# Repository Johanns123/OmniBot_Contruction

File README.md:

# OmniBot_Contruction
 This repository has all the documents of the robot's assembly

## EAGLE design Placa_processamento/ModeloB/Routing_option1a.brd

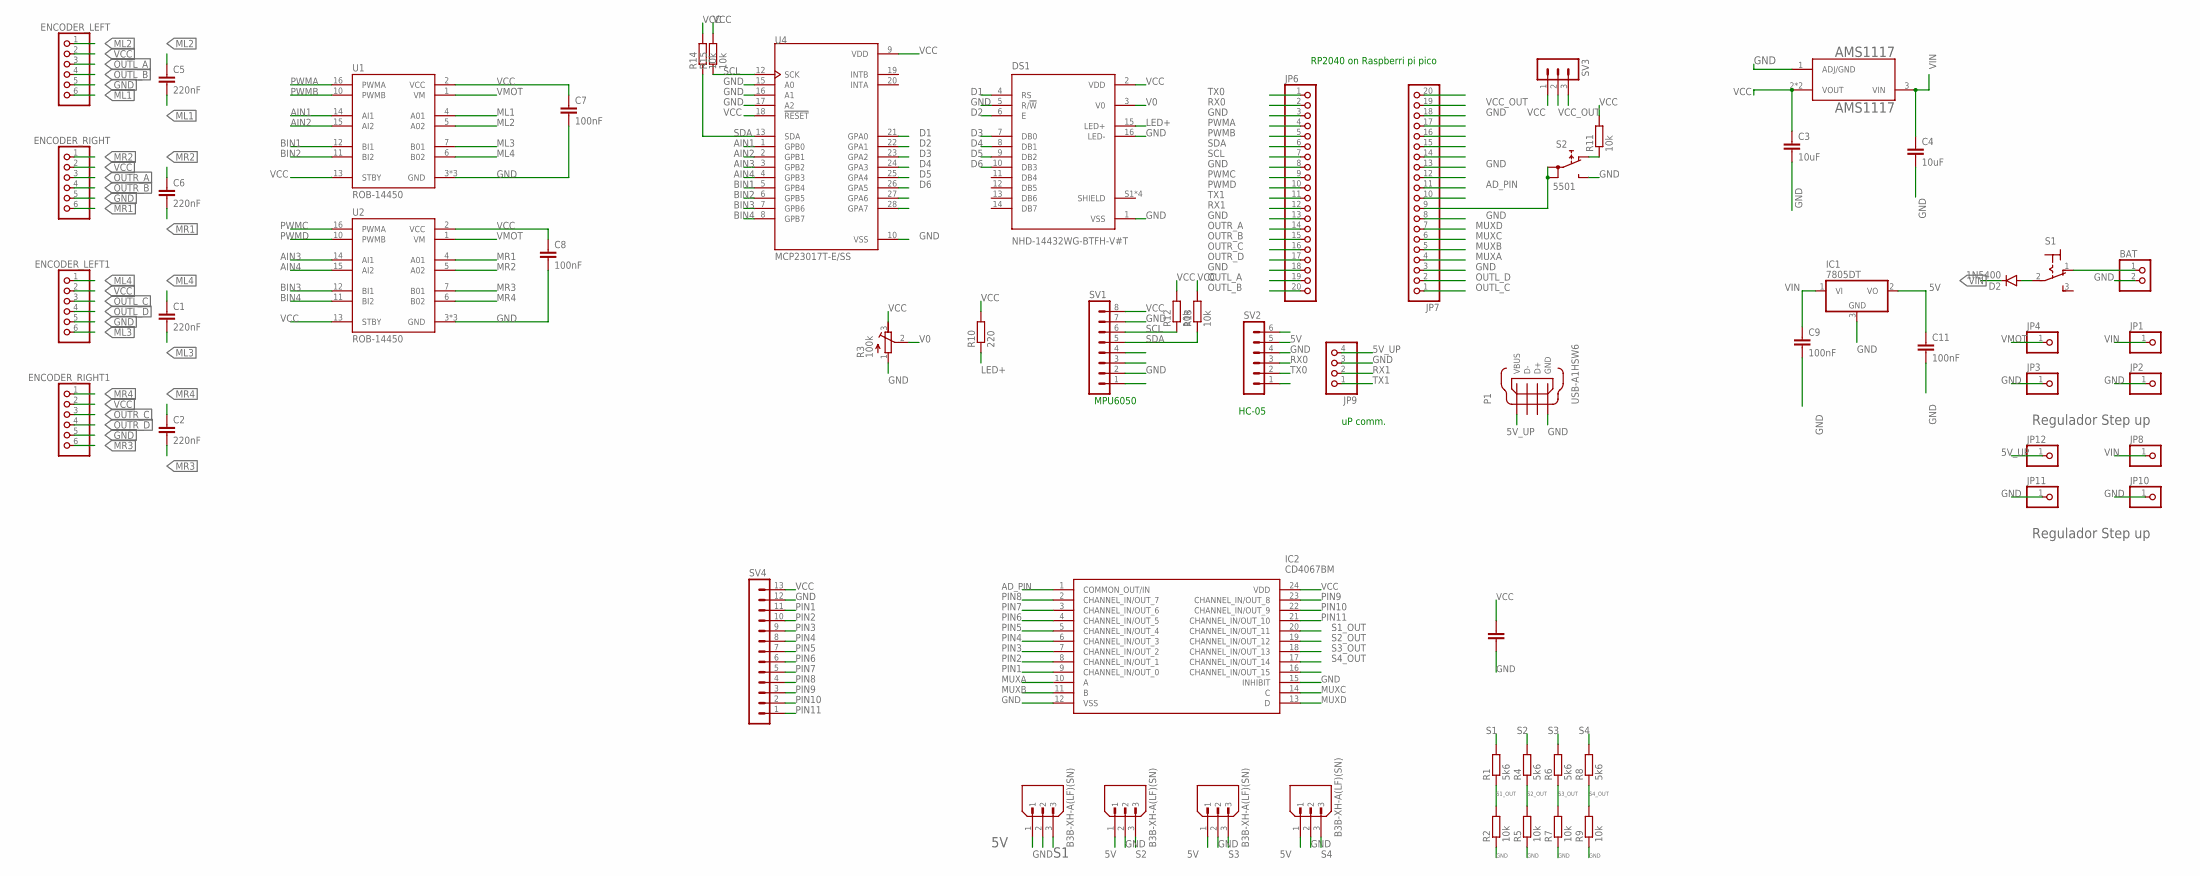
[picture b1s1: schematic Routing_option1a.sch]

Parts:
AMS1117: AMS1117; SOT229P700X180-4N
BAT: PINHD-1X2; 1X02
C1, C2, C5, C6: 220nF; C0805
C3, C4: 10uF; C0805
C7, C8, C9, C10, C11: 100nF; C0805
D2: 1N5400; DO201-15
DIR: B3B-XH-A(LF)(SN); JST_B3B-XH-A(LF)(SN)
DS1: NHD-14432WG-BTFH-V#T; LCD_NHD-14432WG-BTFH-V#T
ENCODER_LEFT, ENCODER_LEFT1: PINHD-1X6; 1X06
ENCODER_RIGHT, ENCODER_RIGHT1: PINHD-1X6; 1X06
ESQ: B3B-XH-A(LF)(SN); JST_B3B-XH-A(LF)(SN)
FRENT: B3B-XH-A(LF)(SN); JST_B3B-XH-A(LF)(SN)
IC1: 7805DT; TO252
IC2: CD4067BM; SOIC127P1030X265-24N
JP1, JP2, JP3, JP4, JP8, JP10, JP11, JP12: PINHD-1X1; 1X01
JP6, JP7: PINHD-1X20; 1X20
JP9: PINHD-1X4; 1X04
P1: USB-A1HSW6; OST_USB-A1HSW6
R1, R4, R6, R8: 5k6; R0805
R2, R5, R7, R9, R11, R12, R13, R14, R15: 10k; R0805
R3: 100k; RTRIM64W
R10: 220; R0805
S1: 320-916
S2: 5501
SV1: MA08-1
SV2: MA06-1
SV3: MA03-1
SV4: MA13-1
TRAS: B3B-XH-A(LF)(SN); JST_B3B-XH-A(LF)(SN)
U1, U2: ROB-14450; MODULE_ROB-14450
U4: MCP23017T-E/SS; SOP65P780X200-28N

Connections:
5V: C11.1, DIR.1, ESQ.1, FRENT.1, IC1.2 (VO), SV2.5, TRAS.1
5V_UP: JP9.4, JP12.1, P1.1 (VBUS)
AD1: JP7.12
AD2: JP7.14
AD_PIN: IC2.1 (COMMON_OUT/IN), JP7.11
AIN1: U1.14 (AI1), U4.1 (GPB0)
AIN2: U1.15 (AI2), U4.2 (GPB1)
AIN3: U2.14 (AI1), U4.3 (GPB2)
AIN4: U2.15 (AI2), U4.4 (GPB3)
BIN1: U1.12 (BI1), U4.5 (GPB4)
BIN2: U1.11 (BI2), U4.6 (GPB5)
BIN3: U2.12 (BI1), U4.7 (GPB6)
BIN4: U2.11 (BI2), U4.8 (GPB7)
D1: DS1.4 (RS), U4.21 (GPA0)
D2: DS1.6 (E), U4.22 (GPA1)
D3: DS1.7 (DB0), U4.23 (GPA2)
D4: DS1.8 (DB1), U4.24 (GPA3)
D5: DS1.9 (DB2), U4.25 (GPA4)
D6: DS1.10 (DB3), U4.26 (GPA5)
GND: AMS1117.1 (ADJ/GND), BAT.2, C3.2, C4.2, C7.2, C8.2, C9.2, C10.2, C11.2, DIR.2, DS1.1 (VSS), DS1.5 (R/!W), DS1.16 (LED-), ENCODER_LEFT.5, ENCODER_LEFT1.5, ENCODER_RIGHT.5, ENCODER_RIGHT1.5, ESQ.2, FRENT.2, IC1.3 (GND), IC2.12 (VSS), IC2.15 (INHIBIT), JP2.1, JP3.1, JP6.3, JP6.8, JP6.13, JP6.18, JP7.3, JP7.8, JP7.13, JP7.18, JP9.3, JP10.1, JP11.1, P1.4 (GND), R2.1, R3.1 (A), R5.1, R7.1, R9.1, S2.NO, SV1.2, SV1.7, SV2.4, SV4.12, TRAS.2, U1.3 (GND), U1.8 (GND), U1.9 (GND), U2.3 (GND), U2.8 (GND), U2.9 (GND), U4.10 (VSS), U4.15 (A0), U4.16 (A1), U4.17 (A2)
LED+: DS1.15 (LED+), R10.1
ML1: C5.2, ENCODER_LEFT.6, U1.4 (A01)
ML2: C5.1, ENCODER_LEFT.1, U1.5 (A02)
ML3: C1.2, ENCODER_LEFT1.6, U1.7 (B01)
ML4: C1.1, ENCODER_LEFT1.1, U1.6 (B02)
MR1: C6.2, ENCODER_RIGHT.6, U2.4 (A01)
MR2: C6.1, ENCODER_RIGHT.1, U2.5 (A02)
MR3: C2.2, ENCODER_RIGHT1.6, U2.7 (B01)
MR4: C2.1, ENCODER_RIGHT1.1, U2.6 (B02)
MUXA: IC2.10 (A), JP7.4
MUXB: IC2.11 (B), JP7.5
MUXC: IC2.14 (C), JP7.6
MUXD: IC2.13 (D), JP7.7
unnamed: D2.A, S1.2
unnamed: BAT.1, S1.1 (O)
unnamed: R11.1, S2.NC
NET$4: JP7.20
NET$5: JP7.17
NET$6: JP7.16
NET$7: JP7.15
NET$8: JP7.10
NET$15: JP7.9, S2.1A, S2.1B
OUTL_A: ENCODER_LEFT.3, JP6.19
OUTL_B: ENCODER_LEFT.4, JP6.20
OUTL_C: ENCODER_LEFT1.3, JP7.1
OUTL_D: ENCODER_LEFT1.4, JP7.2
OUTR_A: ENCODER_RIGHT.3, JP6.14
OUTR_B: ENCODER_RIGHT.4, JP6.15
OUTR_C: ENCODER_RIGHT1.3, JP6.16
OUTR_D: ENCODER_RIGHT1.4, JP6.17
PIN1: IC2.9 (CHANNEL_IN/OUT_0), SV4.11
PIN2: IC2.8 (CHANNEL_IN/OUT_1), SV4.10
PIN3: IC2.7 (CHANNEL_IN/OUT_2), SV4.9
PIN4: IC2.6 (CHANNEL_IN/OUT_3), SV4.8
PIN5: IC2.5 (CHANNEL_IN/OUT_4), SV4.7
PIN6: IC2.4 (CHANNEL_IN/OUT_5), SV4.6
PIN7: IC2.3 (CHANNEL_IN/OUT_6), SV4.5
PIN8: IC2.2 (CHANNEL_IN/OUT_7), SV4.4
PIN9: IC2.23 (CHANNEL_IN/OUT_8), SV4.3
PIN10: IC2.22 (CHANNEL_IN/OUT_9), SV4.2
PIN11: IC2.21 (CHANNEL_IN/OUT_10), SV4.1
PWMA: JP6.4, U1.16 (PWMA)
PWMB: JP6.5, U1.10 (PWMB)
PWMC: JP6.9, U2.16 (PWMA)
PWMD: JP6.10, U2.10 (PWMB)
RX0: JP6.2, SV2.3
RX1: JP6.12, JP9.2
S1: FRENT.3, R1.2
S1_OUT: IC2.20 (CHANNEL_IN/OUT_11), R1.1, R2.2
S2: ESQ.3, R4.2
S2_OUT: IC2.19 (CHANNEL_IN/OUT_12), R4.1, R5.2
S3: DIR.3, R6.2
S3_OUT: IC2.18 (CHANNEL_IN/OUT_13), R6.1, R7.2
S4: R8.2, TRAS.3
S4_OUT: IC2.17 (CHANNEL_IN/OUT_14), R8.1, R9.2
S5: IC2.16 (CHANNEL_IN/OUT_15)
SCL: JP6.7, R12.1, R15.1, SV1.6, U4.12 (SCK)
SDA: JP6.6, R13.1, R14.1, SV1.5, U4.13 (SDA)
TX0: JP6.1, SV2.2
TX1: JP6.11, JP9.1
V0: DS1.3 (V0), R3.2 (S)
VCC: AMS1117.2 (VOUT), AMS1117.4 (VOUT), C3.1, C7.1, C8.1, C10.1, DS1.2 (VDD), ENCODER_LEFT.2, ENCODER_LEFT1.2, ENCODER_RIGHT.2, ENCODER_RIGHT1.2, IC2.24 (VDD), R3.3 (E), R10.2, R11.2, R12.2, R13.2, R14.2, R15.2, SV1.8, SV3.1, SV4.13, U1.2 (VCC), U1.13 (STBY), U2.2 (VCC), U2.13 (STBY), U4.9 (VDD), U4.18 (!RESET)
VCC_OUT: JP7.19, SV3.2
VIN: AMS1117.3 (VIN), C4.1, C9.1, D2.C, IC1.1 (VI), JP1.1, JP8.1
VMOT: JP4.1, U1.1 (VM), U2.1 (VM)

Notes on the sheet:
Regulador Step up
MPU6050
HC-05
uP comm.
RP2040 on Raspberri pi pico

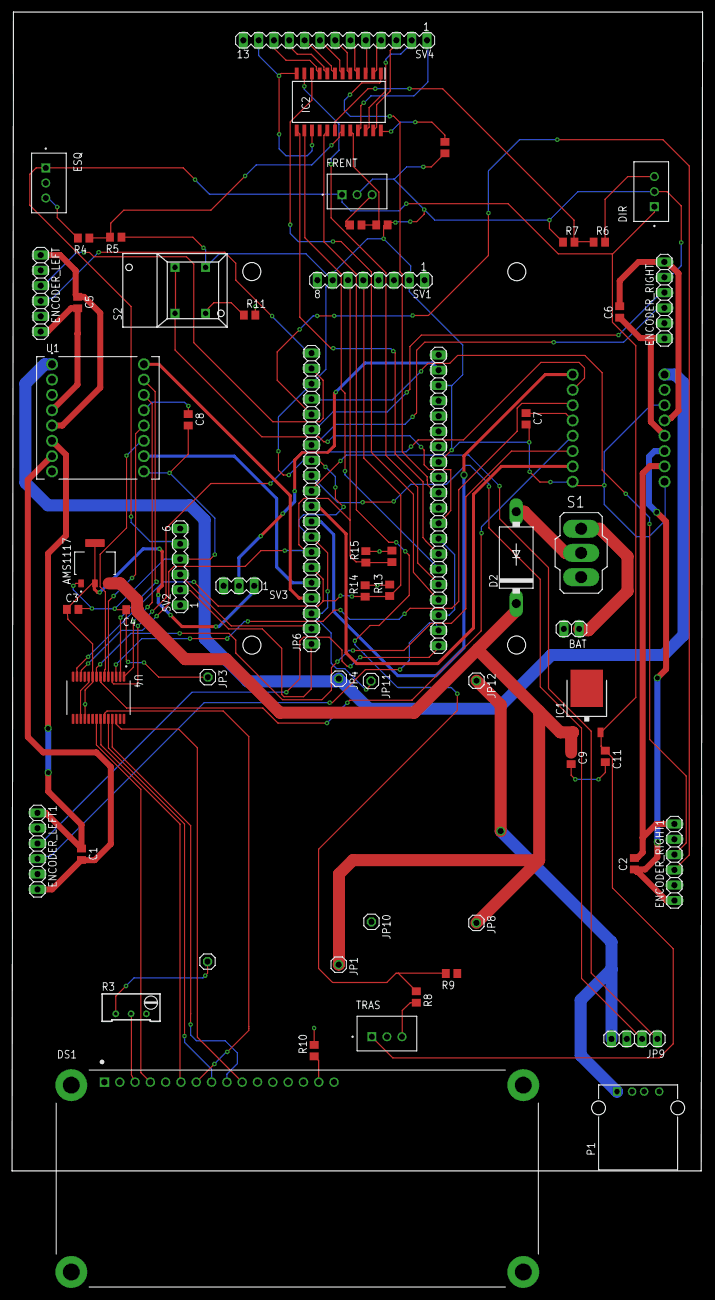
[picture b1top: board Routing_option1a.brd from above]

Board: 2 copper layers, 114.6 x 192.3 mm, 61 parts (1 on the bottom side), 77 nets.

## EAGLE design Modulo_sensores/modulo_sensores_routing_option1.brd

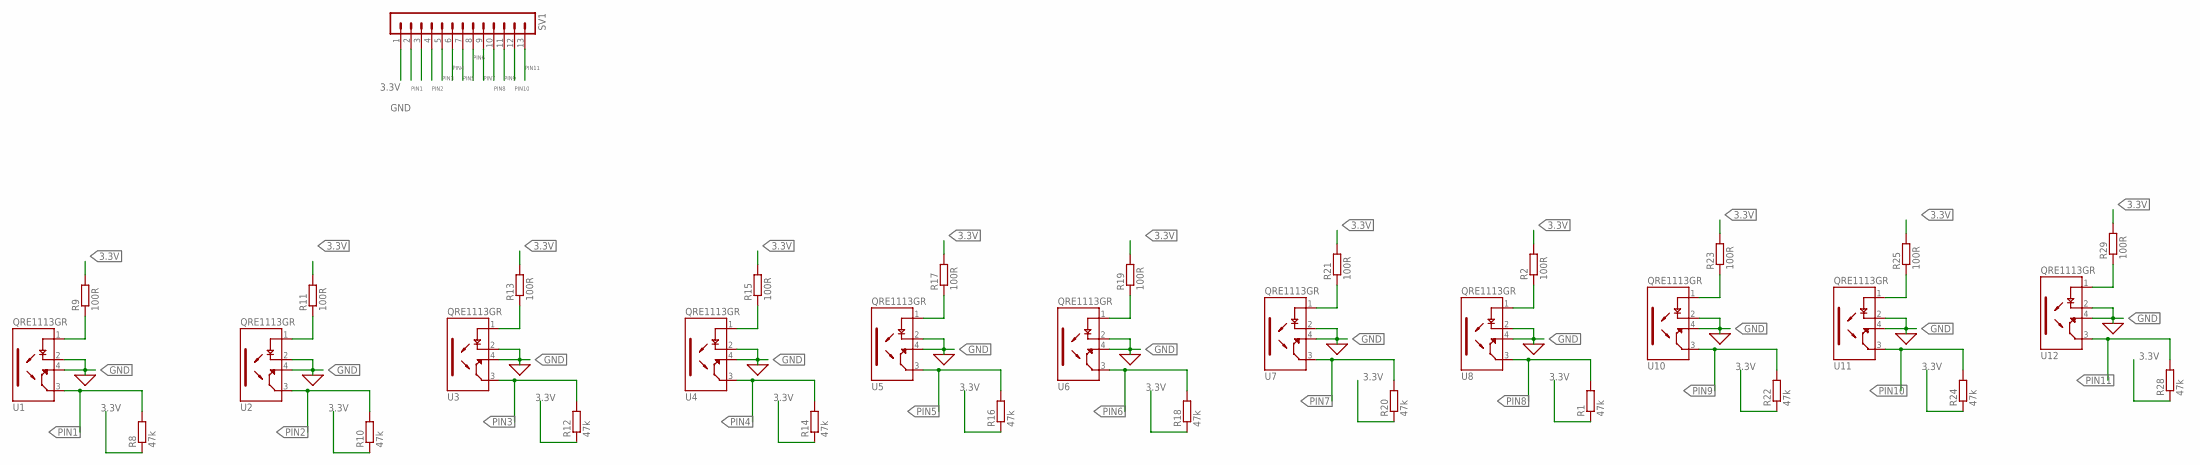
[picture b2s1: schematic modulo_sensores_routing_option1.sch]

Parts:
R1, R8, R10, R12, R14, R16, R18, R20, R22, R24, R28: 47k; M0805
R2, R9, R11, R13, R15, R17, R19, R21, R23, R25, R29: 100R; M0805
SV1: MA13-1
U1, U2, U3, U4, U5, U6, U7, U8, U10, U11, U12: QRE1113GR; SOIC180P460X187-4N

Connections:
3.3V: R1.1, R2.2, R8.1, R9.2, R10.1, R11.2, R12.1, R13.2, R14.1, R15.2, R16.1, R17.2, R18.1, R19.2, R20.1, R21.2, R22.1, R23.2, R24.1, R25.2, R28.1, R29.2, SV1.1
GND: SV1.2, U1.2 (C), U1.4 (ET), U2.2 (C), U2.4 (ET), U3.2 (C), U3.4 (ET), U4.2 (C), U4.4 (ET), U5.2 (C), U5.4 (ET), U6.2 (C), U6.4 (ET), U7.2 (C), U7.4 (ET), U8.2 (C), U8.4 (ET), U10.2 (C), U10.4 (ET), U11.2 (C), U11.4 (ET), U12.2 (C), U12.4 (ET)
unnamed: R9.1, U1.1 (A)
unnamed: R11.1, U2.1 (A)
unnamed: R13.1, U3.1 (A)
unnamed: R15.1, U4.1 (A)
unnamed: R17.1, U5.1 (A)
unnamed: R19.1, U6.1 (A)
unnamed: R21.1, U7.1 (A)
unnamed: R2.1, U8.1 (A)
unnamed: R23.1, U10.1 (A)
unnamed: R25.1, U11.1 (A)
unnamed: R29.1, U12.1 (A)
PIN1: R8.2, SV1.3, U1.3 (CT)
PIN2: R10.2, SV1.4, U2.3 (CT)
PIN3: R12.2, SV1.5, U3.3 (CT)
PIN4: R14.2, SV1.6, U4.3 (CT)
PIN5: R16.2, SV1.7, U5.3 (CT)
PIN6: R18.2, SV1.8, U6.3 (CT)
PIN7: R20.2, SV1.9, U7.3 (CT)
PIN8: R1.2, SV1.10, U8.3 (CT)
PIN9: R22.2, SV1.11, U10.3 (CT)
PIN10: R24.2, SV1.12, U11.3 (CT)
PIN11: R28.2, SV1.13, U12.3 (CT)

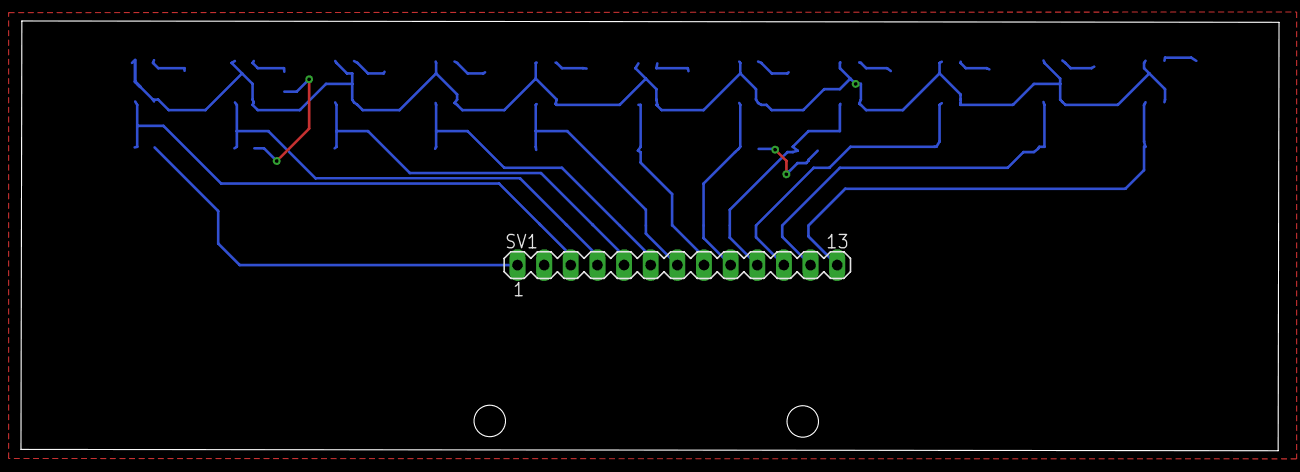
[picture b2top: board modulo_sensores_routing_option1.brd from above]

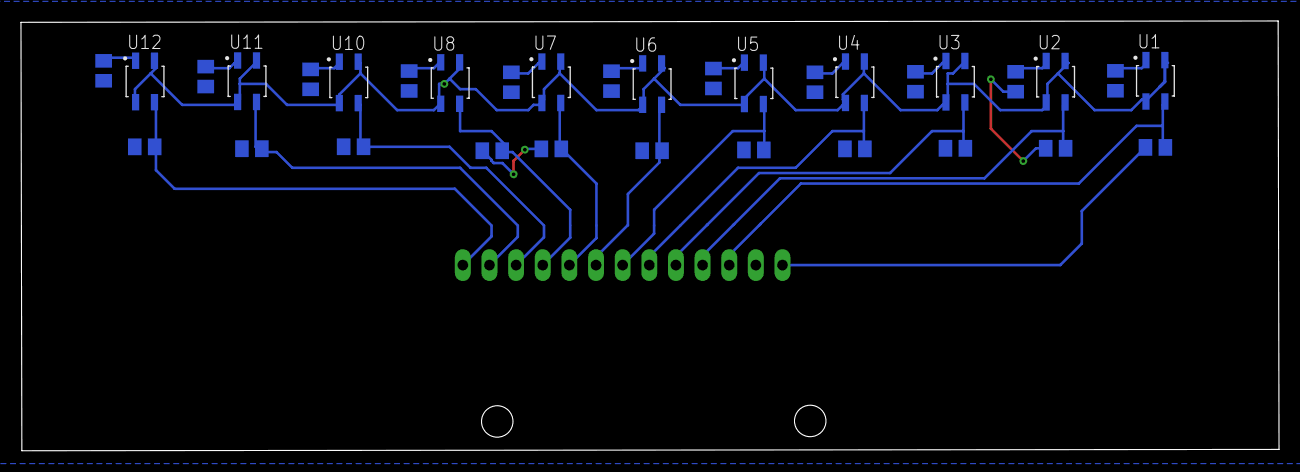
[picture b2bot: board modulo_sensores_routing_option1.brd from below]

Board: 2 copper layers, 120.0 x 41.0 mm, 34 parts (33 on the bottom side), 24 nets.

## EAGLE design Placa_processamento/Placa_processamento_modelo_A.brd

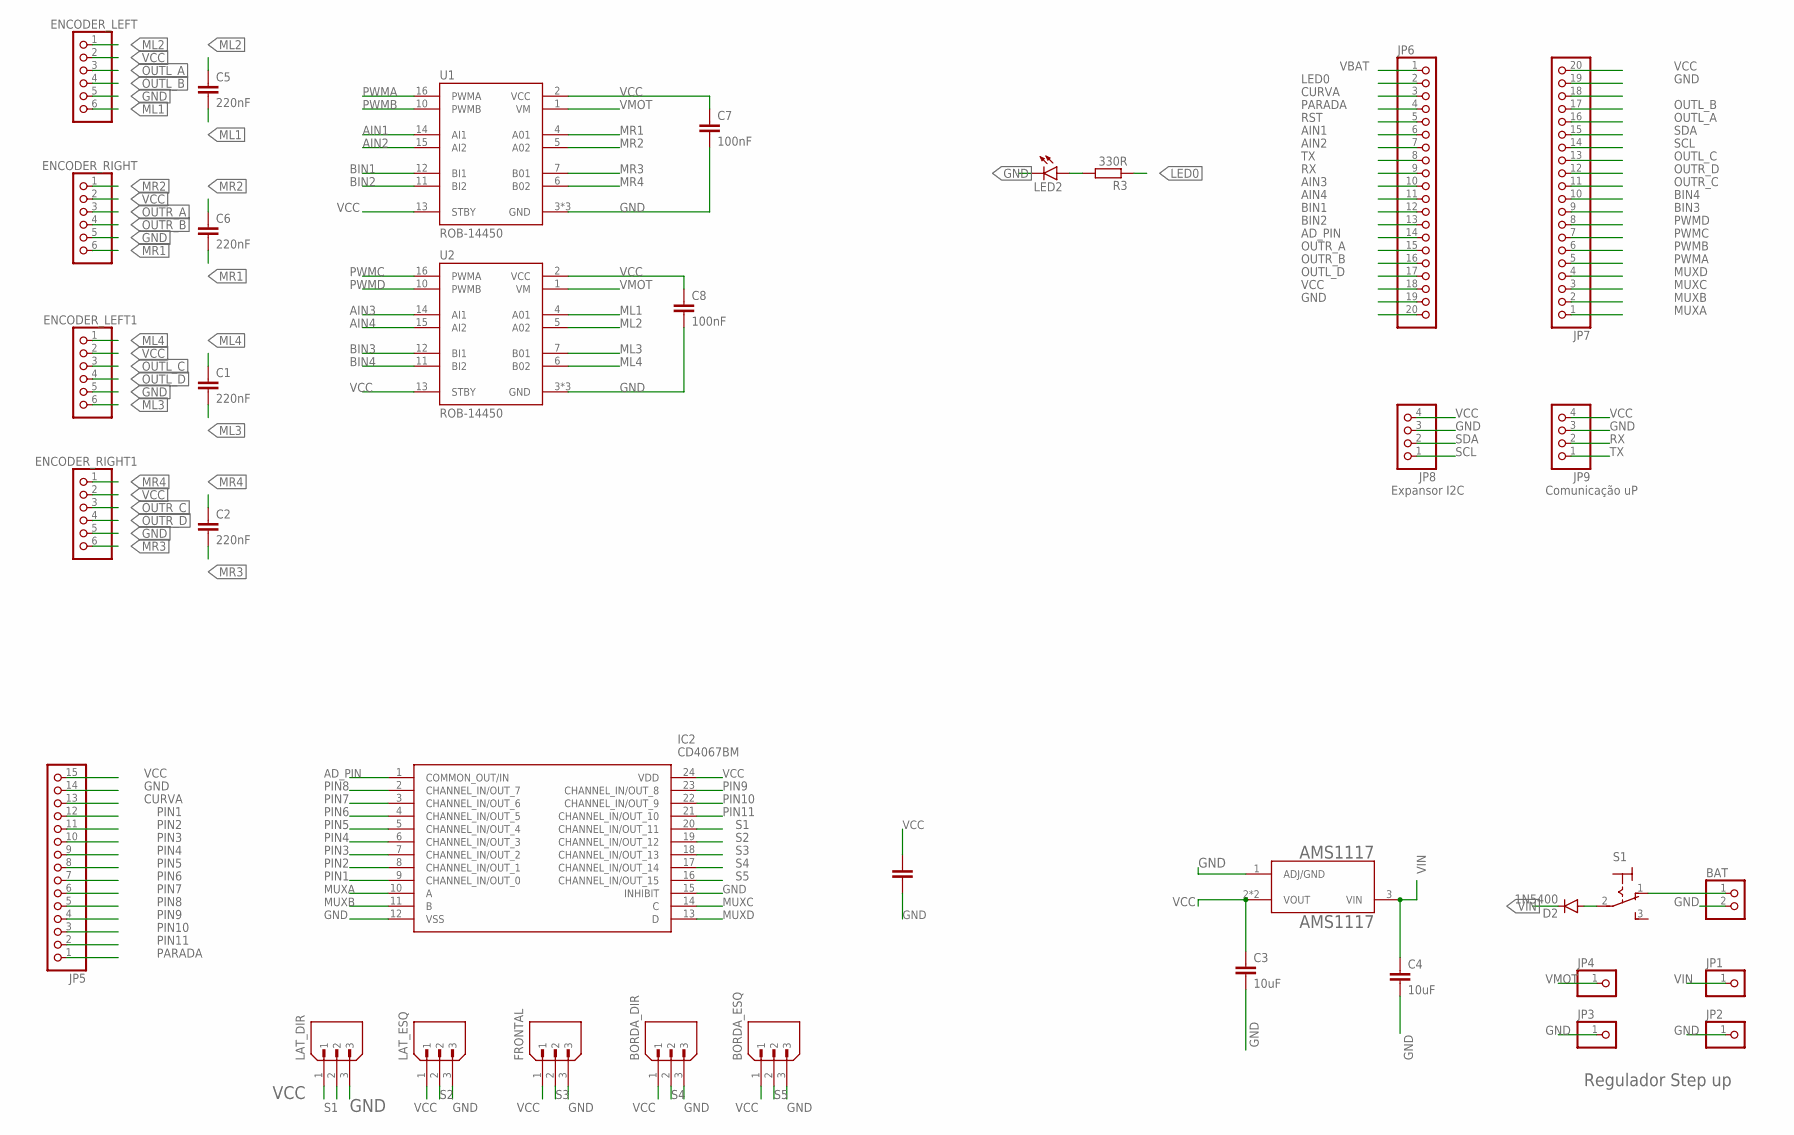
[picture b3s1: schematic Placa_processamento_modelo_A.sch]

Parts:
AMS1117: AMS1117; SOT229P700X180-4N
BAT: PINHD-1X2; 1X02
BORDA_DIR: B3B-XH-A(LF)(SN); JST_B3B-XH-A(LF)(SN)
BORDA_ESQ: B3B-XH-A(LF)(SN); JST_B3B-XH-A(LF)(SN)
C1, C2, C5, C6: 220nF; C0805
C3, C4: 10uF; C0805
C7, C8, C10: 100nF; C0805
D2: 1N5400; DO201-15
ENCODER_LEFT, ENCODER_LEFT1: PINHD-1X6; 1X06
ENCODER_RIGHT, ENCODER_RIGHT1: PINHD-1X6; 1X06
FRONTAL: B3B-XH-A(LF)(SN); JST_B3B-XH-A(LF)(SN)
IC2: CD4067BM; SOIC127P1030X265-24N
JP1, JP2, JP3, JP4: PINHD-1X1; 1X01
JP5: PINHD-1X15; 1X15
JP6, JP7: PINHD-1X20; 1X20
JP8, JP9: PINHD-1X4; 1X04
LAT_DIR: B3B-XH-A(LF)(SN); JST_B3B-XH-A(LF)(SN)
LAT_ESQ: B3B-XH-A(LF)(SN); JST_B3B-XH-A(LF)(SN)
LED2: LEDCHIPLED_0805; CHIPLED_0805
R3: 330R; R0805
S1: 320-916
U1, U2: ROB-14450; MODULE_ROB-14450

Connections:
AD_PIN: IC2.1 (COMMON_OUT/IN), JP6.14
AIN1: JP6.6, U1.14 (AI1)
AIN2: JP6.7, U1.15 (AI2)
AIN3: JP6.10, U2.14 (AI1)
AIN4: JP6.11, U2.15 (AI2)
BIN1: JP6.12, U1.12 (BI1)
BIN2: JP6.13, U1.11 (BI2)
BIN3: JP7.9, U2.12 (BI1)
BIN4: JP7.10, U2.11 (BI2)
CURVA: JP5.13, JP6.3
GND: AMS1117.1 (ADJ/GND), BAT.2, BORDA_DIR.3, BORDA_ESQ.3, C3.2, C4.2, C7.2, C8.2, C10.2, ENCODER_LEFT.5, ENCODER_LEFT1.5, ENCODER_RIGHT.5, ENCODER_RIGHT1.5, FRONTAL.3, IC2.12 (VSS), IC2.15 (INHIBIT), JP2.1, JP3.1, JP5.14, JP6.19, JP7.19, JP8.3, JP9.3, LAT_DIR.3, LAT_ESQ.3, LED2.C, U1.3 (GND), U1.8 (GND), U1.9 (GND), U2.3 (GND), U2.8 (GND), U2.9 (GND)
LED0: JP6.2, R3.1
ML1: C5.2, ENCODER_LEFT.6, U2.4 (A01)
ML2: C5.1, ENCODER_LEFT.1, U2.5 (A02)
ML3: C1.2, ENCODER_LEFT1.6, U2.7 (B01)
ML4: C1.1, ENCODER_LEFT1.1, U2.6 (B02)
MR1: C6.2, ENCODER_RIGHT.6, U1.4 (A01)
MR2: C6.1, ENCODER_RIGHT.1, U1.5 (A02)
MR3: C2.2, ENCODER_RIGHT1.6, U1.7 (B01)
MR4: C2.1, ENCODER_RIGHT1.1, U1.6 (B02)
MUXA: IC2.10 (A), JP7.1
MUXB: IC2.11 (B), JP7.2
MUXC: IC2.14 (C), JP7.3
MUXD: IC2.13 (D), JP7.4
unnamed: D2.A, S1.2
unnamed: BAT.1, S1.1 (O)
unnamed: LED2.A, R3.2
NET: JP7.18
OUTL_A: ENCODER_LEFT.3, JP7.16
OUTL_B: ENCODER_LEFT.4, JP7.17
OUTL_C: ENCODER_LEFT1.3, JP7.13
OUTL_D: ENCODER_LEFT1.4, JP6.17
OUTR_A: ENCODER_RIGHT.3, JP6.15
OUTR_B: ENCODER_RIGHT.4, JP6.16
OUTR_C: ENCODER_RIGHT1.3, JP7.11
OUTR_D: ENCODER_RIGHT1.4, JP7.12
PARADA: JP5.1, JP6.4
PIN1: IC2.9 (CHANNEL_IN/OUT_0), JP5.12
PIN2: IC2.8 (CHANNEL_IN/OUT_1), JP5.11
PIN3: IC2.7 (CHANNEL_IN/OUT_2), JP5.10
PIN4: IC2.6 (CHANNEL_IN/OUT_3), JP5.9
PIN5: IC2.5 (CHANNEL_IN/OUT_4), JP5.8
PIN6: IC2.4 (CHANNEL_IN/OUT_5), JP5.7
PIN7: IC2.3 (CHANNEL_IN/OUT_6), JP5.6
PIN8: IC2.2 (CHANNEL_IN/OUT_7), JP5.5
PIN9: IC2.23 (CHANNEL_IN/OUT_8), JP5.4
PIN10: IC2.22 (CHANNEL_IN/OUT_9), JP5.3
PIN11: IC2.21 (CHANNEL_IN/OUT_10), JP5.2
PWMA: JP7.5, U1.16 (PWMA)
PWMB: JP7.6, U1.10 (PWMB)
PWMC: JP7.7, U2.16 (PWMA)
PWMD: JP7.8, U2.10 (PWMB)
RST: JP6.5
RX: JP6.9, JP9.2
S1: IC2.20 (CHANNEL_IN/OUT_11), LAT_DIR.2
S2: IC2.19 (CHANNEL_IN/OUT_12), LAT_ESQ.2
S3: FRONTAL.2, IC2.18 (CHANNEL_IN/OUT_13)
S4: BORDA_DIR.2, IC2.17 (CHANNEL_IN/OUT_14)
S5: BORDA_ESQ.2, IC2.16 (CHANNEL_IN/OUT_15)
SCL: JP7.14, JP8.1
SDA: JP7.15, JP8.2
TX: JP6.8, JP9.1
VBAT: JP6.1
VCC: AMS1117.2 (VOUT), AMS1117.4 (VOUT), BORDA_DIR.1, BORDA_ESQ.1, C3.1, C7.1, C8.1, C10.1, ENCODER_LEFT.2, ENCODER_LEFT1.2, ENCODER_RIGHT.2, ENCODER_RIGHT1.2, FRONTAL.1, IC2.24 (VDD), JP5.15, JP6.18, JP7.20, JP8.4, JP9.4, LAT_DIR.1, LAT_ESQ.1, U1.2 (VCC), U1.13 (STBY), U2.2 (VCC), U2.13 (STBY)
VIN: AMS1117.3 (VIN), C4.1, D2.C, JP1.1
VMOT: JP4.1, U1.1 (VM), U2.1 (VM)

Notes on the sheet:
Regulador Step up
Expansor I2C
Comunicação uP

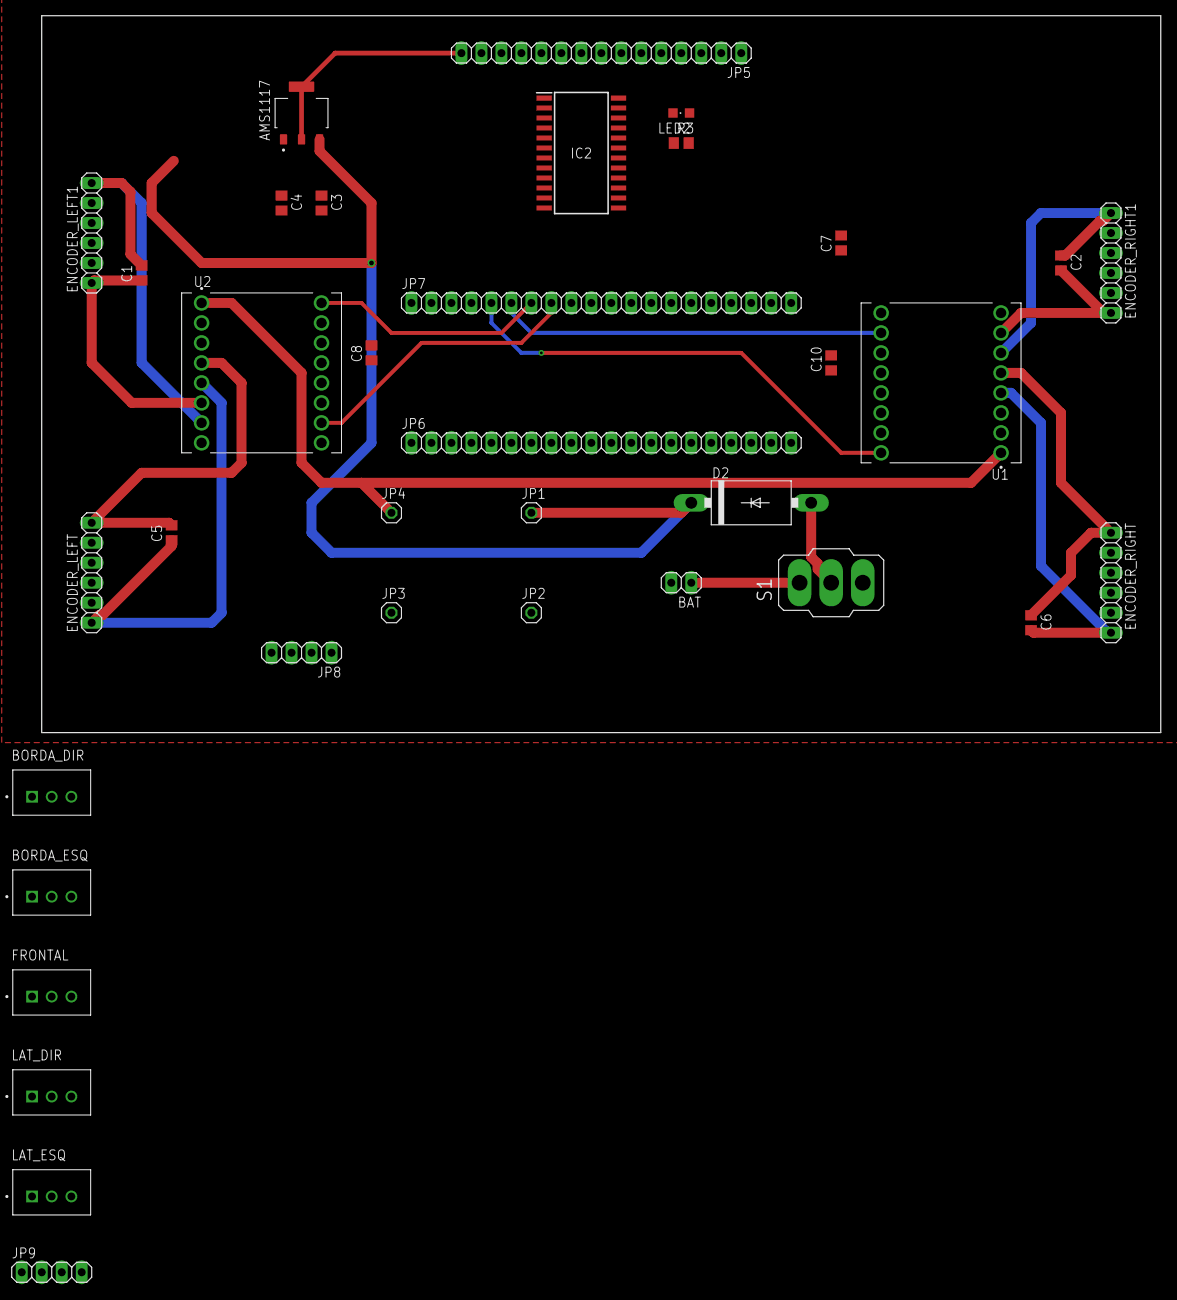
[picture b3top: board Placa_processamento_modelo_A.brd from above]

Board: 2 copper layers, 142.2 x 91.1 mm, 36 parts (0 on the bottom side), 63 nets.

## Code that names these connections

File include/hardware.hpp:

#include <stdio.h>
#include <string.h>
#include <stdlib.h>
#include <pico/stdlib.h>
#include <hardware/adc.h>
#include <hardware/pwm.h>
#include <hardware/irq.h>
#include <hardware/dma.h>
#include <hardware/i2c.h>
#include <hardware/uart.h>
#include <mcp23017.h>
#include "MPU6050.h"

#ifndef HARDWARE
#define HARDWARE

#define MCP23017_I2C_ADDRESS 0x20
#define TIMER0_INTERVAL_MS 1
#define NUM_SENSORS 16

/*mapeamento de hardware*/
/*=====================*/
#define TX0     0
#define RX0     1
#define PWMA    2
#define PWMB    3
#define SDA     4
#define SCL     5
#define PWMC    6
#define PWMD    7
#define TX1     8
#define RX1     9
#define OUTR_A  10
#define OUTR_B  11
#define OUTR_C  12
#define OUTR_D  13
#define OUTL_A  14
#define OUTL_B  15
#define OUTL_C  16
#define OUTL_D  17
#define MUXA    18
#define MUXB    19
#define MUXC    20
#define MUXD    21
#define BUTTON  22
#define AD_PIN  26
#define BATT    27

#define AIN1 (0 + 8) //motor esq1 tras
#define AIN2 (1 + 8) //motor esq1 frente
#define AIN3 (2 + 8) //motor dir1 frente
#define AIN4 (3 + 8) //motor dir1 tras
#define BIN1 (4 + 8) //motor esq2 tras
#define BIN2 (5 + 8) //motor esq2 frente
#define BIN3 (6 + 8) //motor dir1 frente
#define BIN4 (7 + 8) //motor dir1 tras

#define UART_ID uart0 
#define BAUD_RATE 115200
#define DATA_BITS 8
#define STOP_BITS 1
#define PARITY UART_PARITY_NONE

extern uint16_t slice_pwma, slice_pwmb, slice_pwmc, slice_pwmd;

extern const uint PWM_FREQ;  // Frequência PWM desejada (2kHz)
extern const uint PWM_RANGE;  // Resolução do PWM (12 bits)

extern i2c_inst_t *i2c;
extern Mcp23017 extender;

void gpio_config(void);
void adc_config(void);
void pwm_init(void);
void uart0_config(void);
void i2c_config(void);

#endif

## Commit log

2024-01-24 Remocao de arquivos lixo
2024-01-31 code for educational purposes
